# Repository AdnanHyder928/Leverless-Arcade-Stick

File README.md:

I am currently in the process of designing a custom Arcade Stick PCB. The MCU I chose for this project is the Atmega32U4. 

<h1 align="center">PHASE 1</h1>
This is how the schematic is currently looking like:

I am still working on the schematic portion and have not yet started with the PCB Design part.

<h1 align="center">Initial Case Design (AutoCAD)</h1>

<h1>UPDATE</h1>

<p>I managed to update the schematic of the push buttons, as the previous arrangement was incorrect.</p>

<p>I also connected a 16MHz crystal to the ATMega32U4 schematic for removing any sort of delay with the input of the buttons.</p>

<h1>Case Layout Updated (2D View)</h1>

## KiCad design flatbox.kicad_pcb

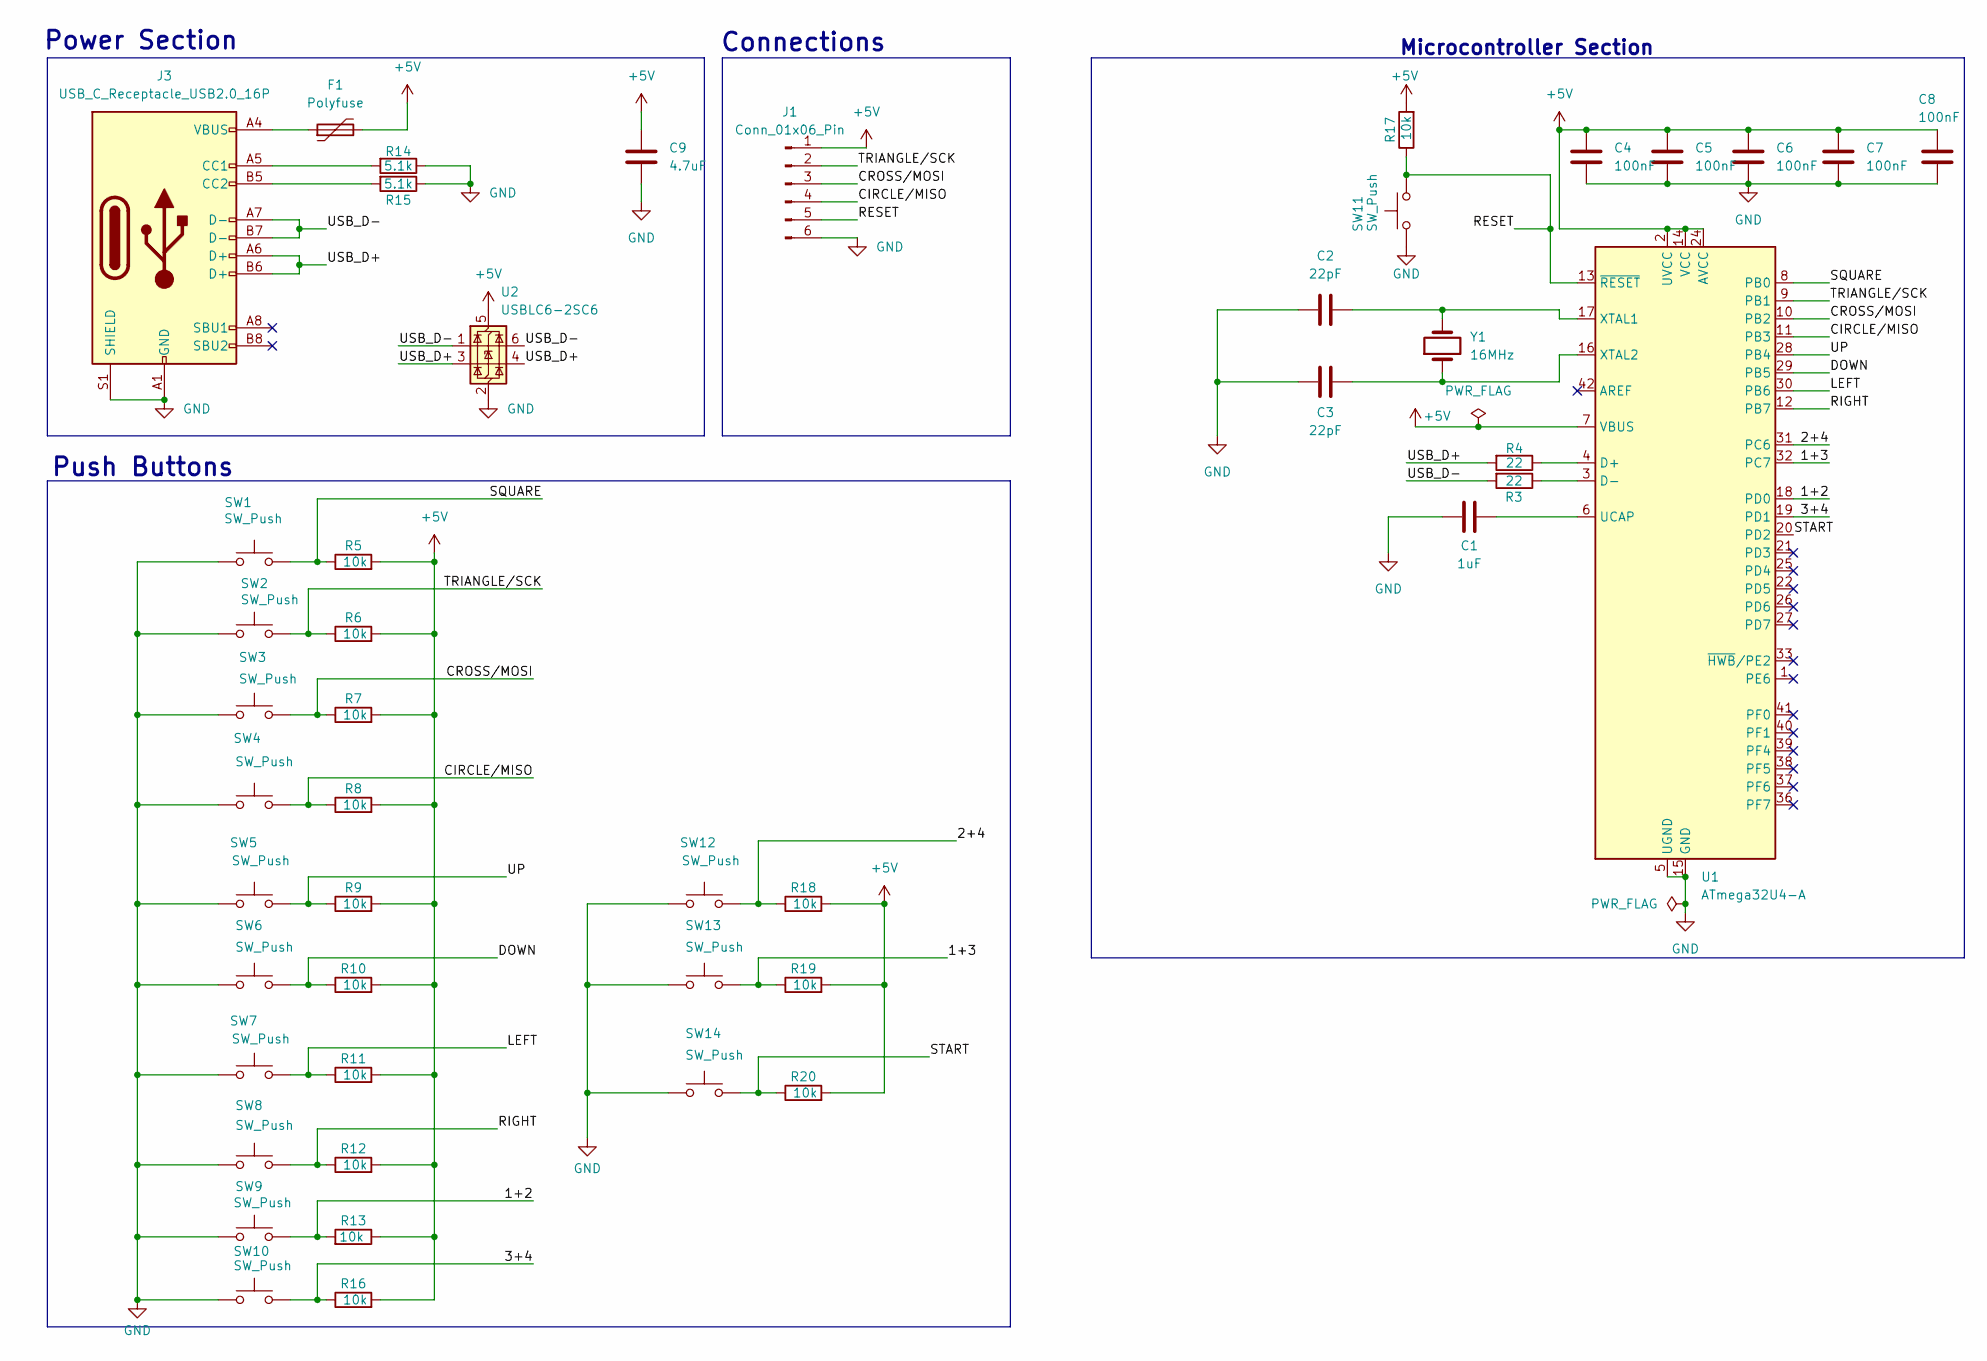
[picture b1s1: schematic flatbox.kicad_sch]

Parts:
C1: 1uF; C_0805_2012Metric
C2, C3: 22pF; C_0805_2012Metric
C4, C5, C6, C7, C8: 100nF; C_0805_2012Metric
C9: 4.7uF; C_0805_2012Metric
F1: Polyfuse; Fuse_1206_3216Metric_Pad1.42x1.75mm_HandSolder
J1: Conn_01x06_Pin; PinHeader_1x06_P2.54mm_Vertical
J3: USB_C_Receptacle_USB2.0_16P; USB_C_Receptacle_HRO_TYPE-C-31-M-12
R3, R4: 22; R_0805_2012Metric
R5, R6, R7, R8, R9, R10, R11, R12, R13, R16, R17, R18, R19, R20: 10k; R_0805_2012Metric
R14, R15: 5.1k; R_0805_2012Metric
SW1, SW2, SW3, SW4, SW5, SW6, SW7, SW8, SW9, SW10, SW11, SW12, SW13, SW14: SW_Push; SW_Cherry_MX_1.00u_PCB
U1: ATmega32U4-A; TQFP-44_10x10mm_P0.8mm
U2: USBLC6-2SC6; SOT-23-6
Y1: 16MHz; Crystal_HC49-4H_Vertical

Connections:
+5V: C4.2, C5.2, C6.2, C7.2, C8.2, C9.2, F1.2, J1.1, R5.2, R6.2, R7.2, R8.2, R9.2, R10.2, R11.2, R12.2, R13.1, R16.2, R17.2, R18.2, R19.2, R20.2, U1.2 (UVCC), U1.7 (VBUS), U1.14 (VCC), U1.24 (AVCC), U1.34 (VCC), U1.44 (AVCC), U2.5 (VBUS)
/1+2: R13.2, SW9.2, U1.18 (PD0)
/1+3: R19.1, SW13.2, U1.32 (PC7)
/2+4: R18.1, SW12.2, U1.31 (PC6)
/3+4: R16.1, SW10.2, U1.19 (PD1)
/CIRCLE/MISO: J1.4, R8.1, SW4.2, U1.11 (PB3)
/CROSS/MOSI: J1.3, R7.1, SW3.2, U1.10 (PB2)
/DOWN: R10.1, SW6.2, U1.29 (PB5)
/LEFT: R11.1, SW7.2, U1.30 (PB6)
/RESET: J1.5, R17.1, SW11.2, U1.13 (~RESET)
/RIGHT: R12.1, SW8.2, U1.12 (PB7)
/SQUARE: R5.1, SW1.2, U1.8 (PB0)
/START: R20.1, SW14.2, U1.20 (PD2)
/TRIANGLE/SCK: J1.2, R6.1, SW2.2, U1.9 (PB1)
/UP: R9.1, SW5.2, U1.28 (PB4)
/USB_D+: J3.A6 (D+), J3.B6 (D+), R4.2, U2.3 (I/O2), U2.4 (I/O2)
/USB_D-: J3.A7 (D-), J3.B7 (D-), R3.2, U2.1 (I/O1), U2.6 (I/O1)
GND: C1.1, C2.1, C3.1, C4.1, C5.1, C6.1, C7.1, C8.1, C9.1, J1.6, J3.A1 (GND), J3.A12 (GND), J3.B1 (GND), J3.B12 (GND), J3.S1 (SHIELD), R14.1, R15.1, SW1.1, SW2.1, SW3.1, SW4.1, SW5.1, SW6.1, SW7.1, SW8.1, SW9.1, SW10.1, SW11.1, SW12.1, SW13.1, SW14.1, U1.5 (UGND), U1.15 (GND), U1.23 (GND), U1.35 (GND), U1.43 (GND), U2.2 (GND)
unnamed: F1.1, J3.A4 (VBUS), J3.A9 (VBUS), J3.B4 (VBUS), J3.B9 (VBUS)
unnamed: J3.A5 (CC1), R14.2
unnamed: J3.B5 (CC2), R15.2
unnamed: R4.1, U1.4 (D+)
unnamed: R3.1, U1.3 (D-)
unnamed: C1.2, U1.6 (UCAP)
unnamed: C2.2, U1.17 (XTAL1), Y1.2
unnamed: C3.2, U1.16 (XTAL2), Y1.1

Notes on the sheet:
Power Section
Microcontroller Section
Push Buttons
Connections

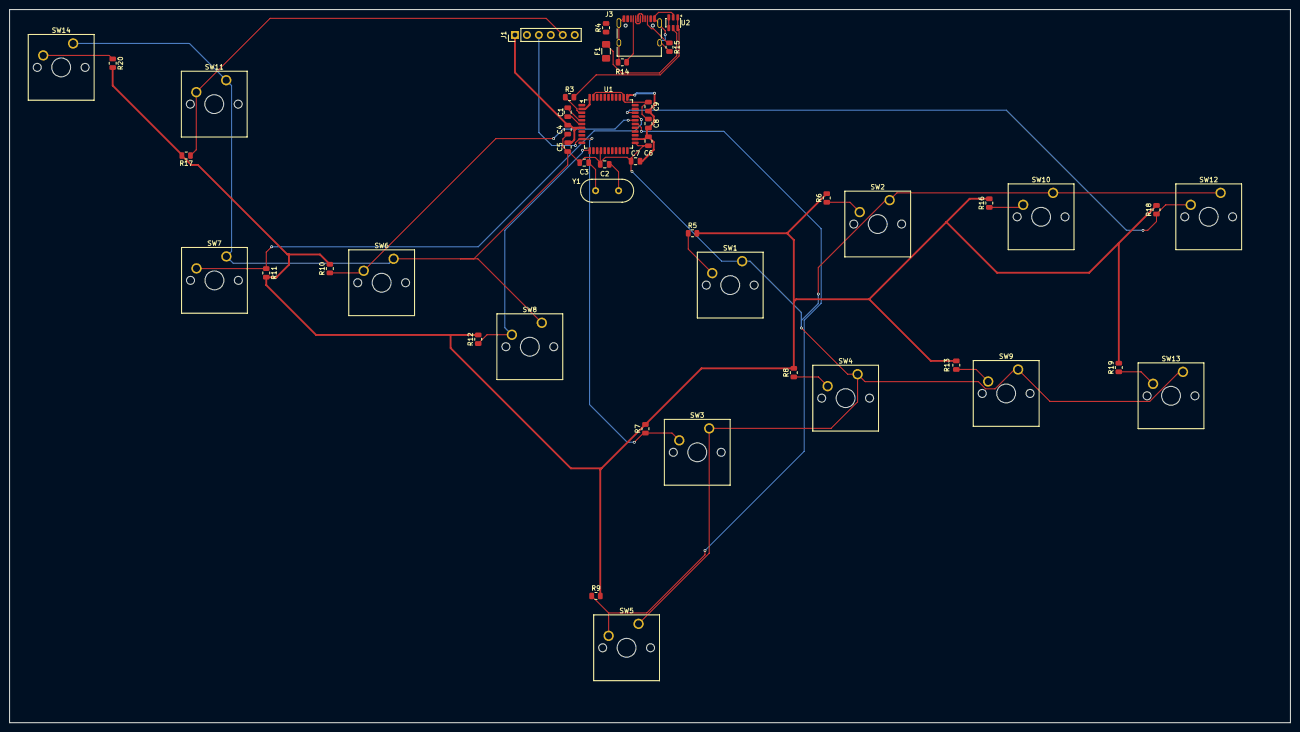
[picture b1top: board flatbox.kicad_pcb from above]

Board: 2 copper layers, 271.9 x 151.4 mm, 47 parts (0 on the bottom side), 26 nets.

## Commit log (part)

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2025-12-01 Schematic still in progress, working on PCB not yet started
2025-12-01 Add project description for custom Arcade Stick PCB
2025-12-01 Update README with project phase and schematic
    Added project phase details and schematic image.
2025-12-05 README updated
    Added initial case design section with images.
2025-12-23 Second Commit done, some updates to the schematic have been made
2025-12-24 README updated
    Updated the schematic of the push buttons and added new images.
2025-12-24 Updated README with new case layout screenshot
